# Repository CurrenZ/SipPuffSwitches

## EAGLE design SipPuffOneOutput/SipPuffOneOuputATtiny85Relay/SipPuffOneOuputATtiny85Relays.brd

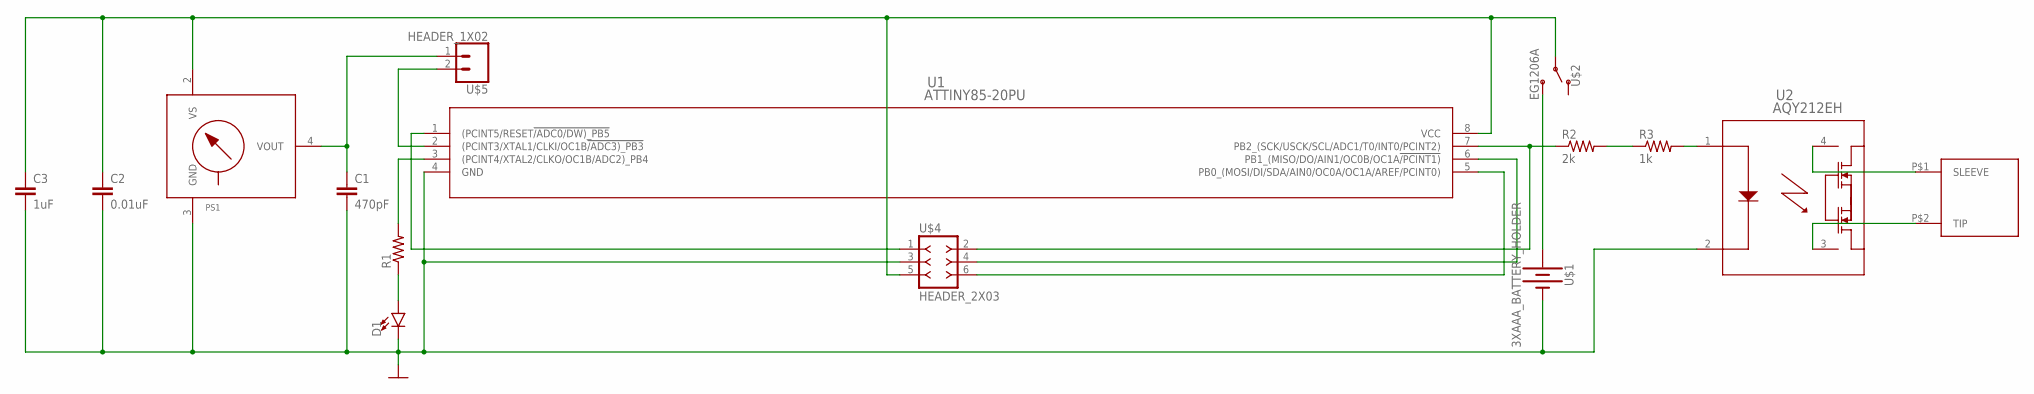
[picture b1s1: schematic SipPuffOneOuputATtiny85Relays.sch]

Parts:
C1: 470pF; CAP-PTH-SMALL-KIT
C2: 0.01uF; CAP-PTH-SMALL-KIT
C3: 1uF; CAP-PTH-SMALL-KIT
D1: LED5MM; LED_5MM
PS1: MPX-1351; 1351
R1: RESISTOR_R-US_; RESISTOR_0207/10
R2: 2k; RESISTOR_0207/10
R3: 1k; RESISTOR_0207/10
U1: ATTINY85-20PU; 8P3
U2: AQY212EH; PAN_AQY21-DIP4
U$1: 3XAAA_BATTERY_HOLDER
U$2: EG1206A
U$3: MONO_WIRE
U$4: HEADER_2X03; 2X3
U$5: HEADER_1X02; 1X02

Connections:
GND: C1.2, C2.2, C3.2, D1.K (C), PS1.3 (GND), U1.4 (GND), U2.2, U$1.P$2 (-), U$4.3
unnamed: C1.1, PS1.4 (VOUT), U$5.1
unnamed: C2.1, C3.1, PS1.2 (VS), U1.8 (VCC), U$2.2, U$4.5
unnamed: U$1.P$1 (+), U$2.3 (S)
unnamed: R1.2, U1.3 ((PCINT4/XTAL2/CLKO/OC1B/ADC2)_PB4)
unnamed: D1.A, R1.1
unnamed: R2.1, U1.7 (PB2_(SCK/USCK/SCL/ADC1/T0/INT0/PCINT2)), U$4.2
unnamed: U2.4, U$3.P$1 (SLEEVE)
unnamed: U2.3, U$3.P$2 (TIP)
unnamed: U1.1 ((PCINT5/RESET!/ADC0/DW)_PB5), U$4.1
unnamed: U1.2 ((PCINT3/XTAL1/CLKI/OC1B!/ADC3)_PB3), U$5.2
unnamed: R2.2, R3.1
unnamed: U1.6 (PB1_(MISO/DO/AIN1/OC0B/OC1A!/PCINT1)), U$4.4
unnamed: U1.5 (PB0_(MOSI/DI/SDA/AIN0/OC0A/OC1A/AREF/PC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), U$4.6
unnamed: R3.2, U2.1

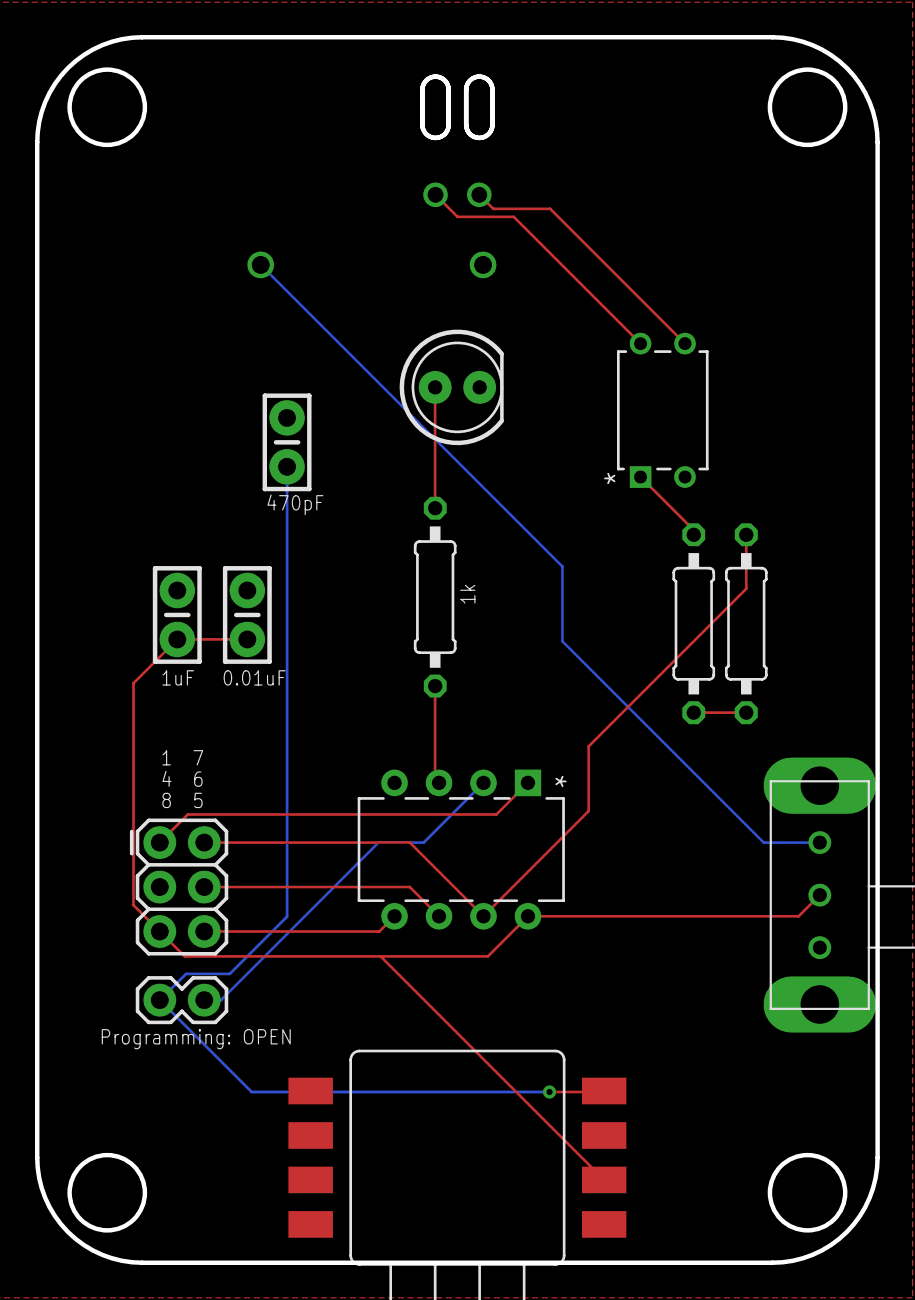
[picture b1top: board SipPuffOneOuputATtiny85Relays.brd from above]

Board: 2 copper layers, 48.0 x 70.0 mm, 15 parts (1 on the bottom side), 15 nets.

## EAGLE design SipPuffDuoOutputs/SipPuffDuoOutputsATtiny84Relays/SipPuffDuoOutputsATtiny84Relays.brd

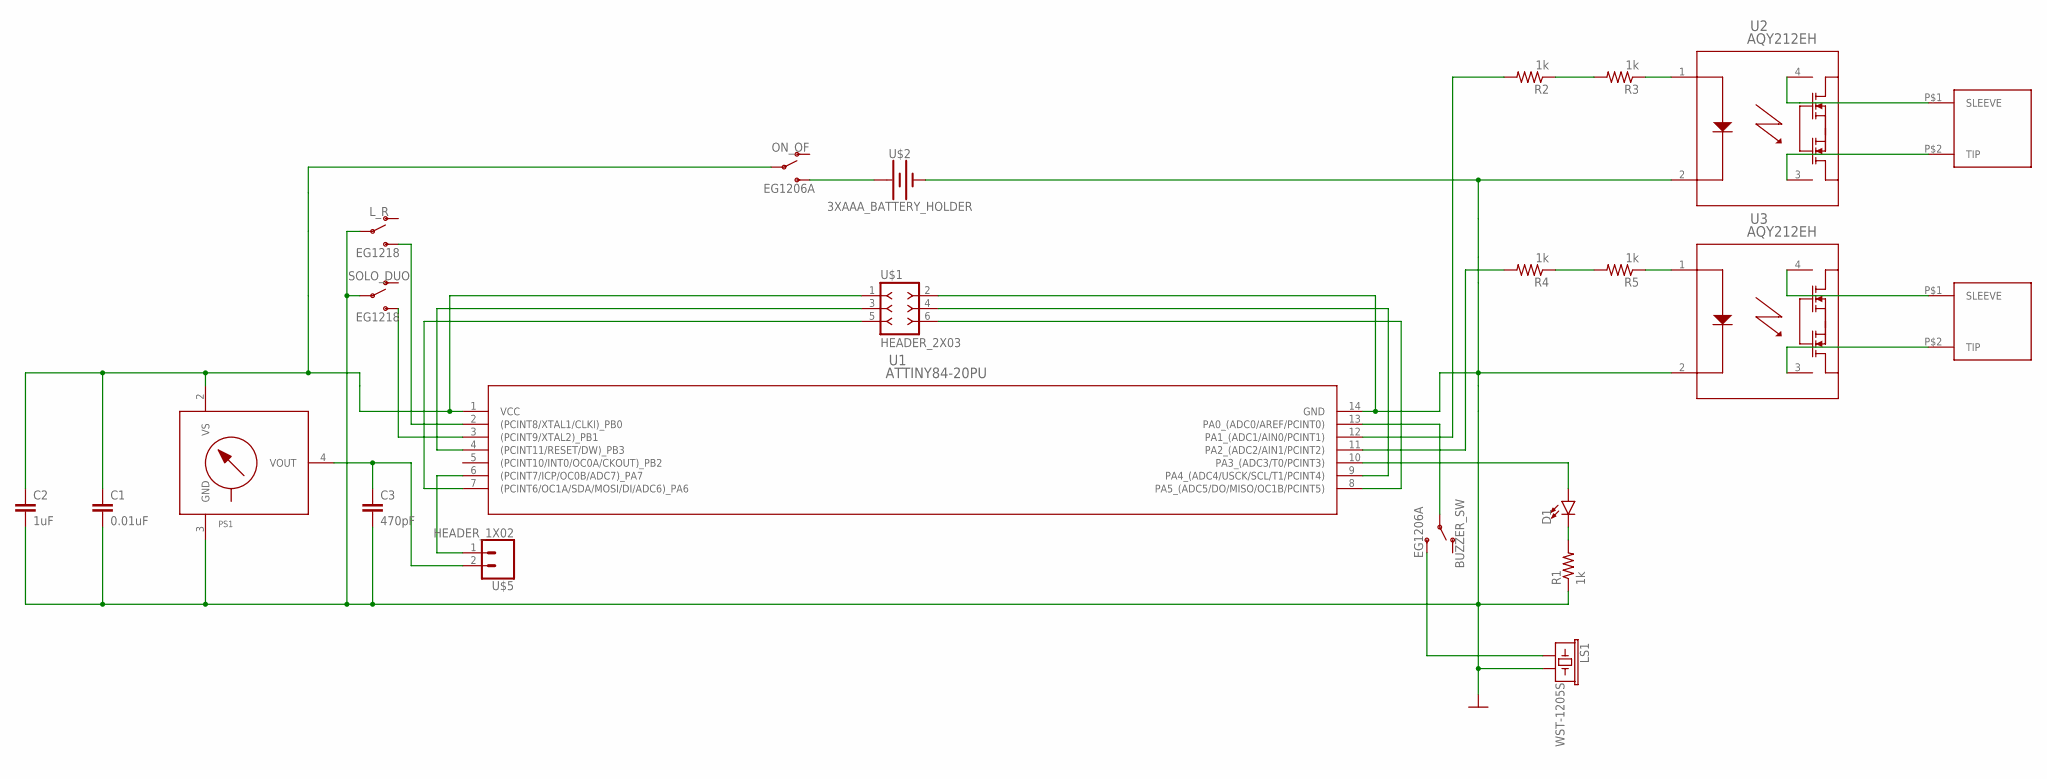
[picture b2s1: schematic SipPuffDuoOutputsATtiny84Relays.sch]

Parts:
BUZZER_SW: EG1206A
C1: 0.01uF; CAP-PTH-SMALL-KIT
C2: 1uF; CAP-PTH-SMALL-KIT
C3: 470pF; CAP-PTH-SMALL-KIT
D1: LED5MM; LED_5MM
LS1: WST-1205S; BUZZER-12MM
L_R: EG1218
ON_OF: EG1206A
PS1: MPX-1351; 1351
R1, R2, R3, R4, R5: 1k; RESISTOR_0207/10
SOLO_DUO: EG1218
U1: ATTINY84-20PU; 14P3
U2, U3: AQY212EH; PAN_AQY21-DIP4
U$1: HEADER_2X03; 2X3
U$2: 3XAAA_BATTERY_HOLDER
U$3, U$4: MONO_WIRE
U$5: HEADER_1X02; 1X02

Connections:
5V: C1.1, C2.1, ON_OF.2, PS1.2 (VS), U1.1 (VCC), U$1.1
GND: C1.2, C2.2, C3.2, LS1.- (2), L_R.2, PS1.3 (GND), R1.1, SOLO_DUO.2, U1.14 (GND), U2.2, U3.2, U$1.2, U$2.P$2 (-)
MPXVOUT: C3.1, PS1.4 (VOUT), U$5.2
unnamed: D1.A, U1.10 (PA3_(ADC3/T0/PCINT3))
unnamed: R2.2, U1.12 (PA1_(ADC1/AIN0/PCINT1))
unnamed: L_R.3 (S), U1.2 ((PCINT8/XTAL1/CLKI)_PB0)
unnamed: R4.2, U1.11 (PA2_(ADC2/AIN1/PCINT2))
unnamed: SOLO_DUO.3 (S), U1.3 ((PCINT9/XTAL2)_PB1)
unnamed: U1.8 (PA5_(ADC5/DO/MISO/OC1B/PCINT5)), U$1.6
unnamed: D1.K (C), R1.2
unnamed: U1.4 ((PCINT11/RESET/DW)_PB3), U$1.3
unnamed: U1.9 (PA4_(ADC4/USCK/SCL/T1/PCINT4)), U$1.4
unnamed: U1.7 ((PCINT6/OC1A/SDA/MOSI/DI/ADC6)_PA6), U$1.5
unnamed: ON_OF.3 (S), U$2.P$1 (+)
unnamed: BUZZER_SW.3 (S), LS1.+ (1)
unnamed: BUZZER_SW.2, U1.13 (PA0_(ADC0/AREF/PCINT0))
unnamed: U2.4, U$3.P$1 (SLEEVE)
unnamed: U2.3, U$3.P$2 (TIP)
unnamed: U3.4, U$4.P$1 (SLEEVE)
unnamed: U3.3, U$4.P$2 (TIP)
unnamed: U1.6 ((PCINT7/ICP/OC0B/ADC7)_PA7), U$5.1
unnamed: R2.1, R3.2
unnamed: R3.1, U2.1
unnamed: R4.1, R5.2
unnamed: R5.1, U3.1

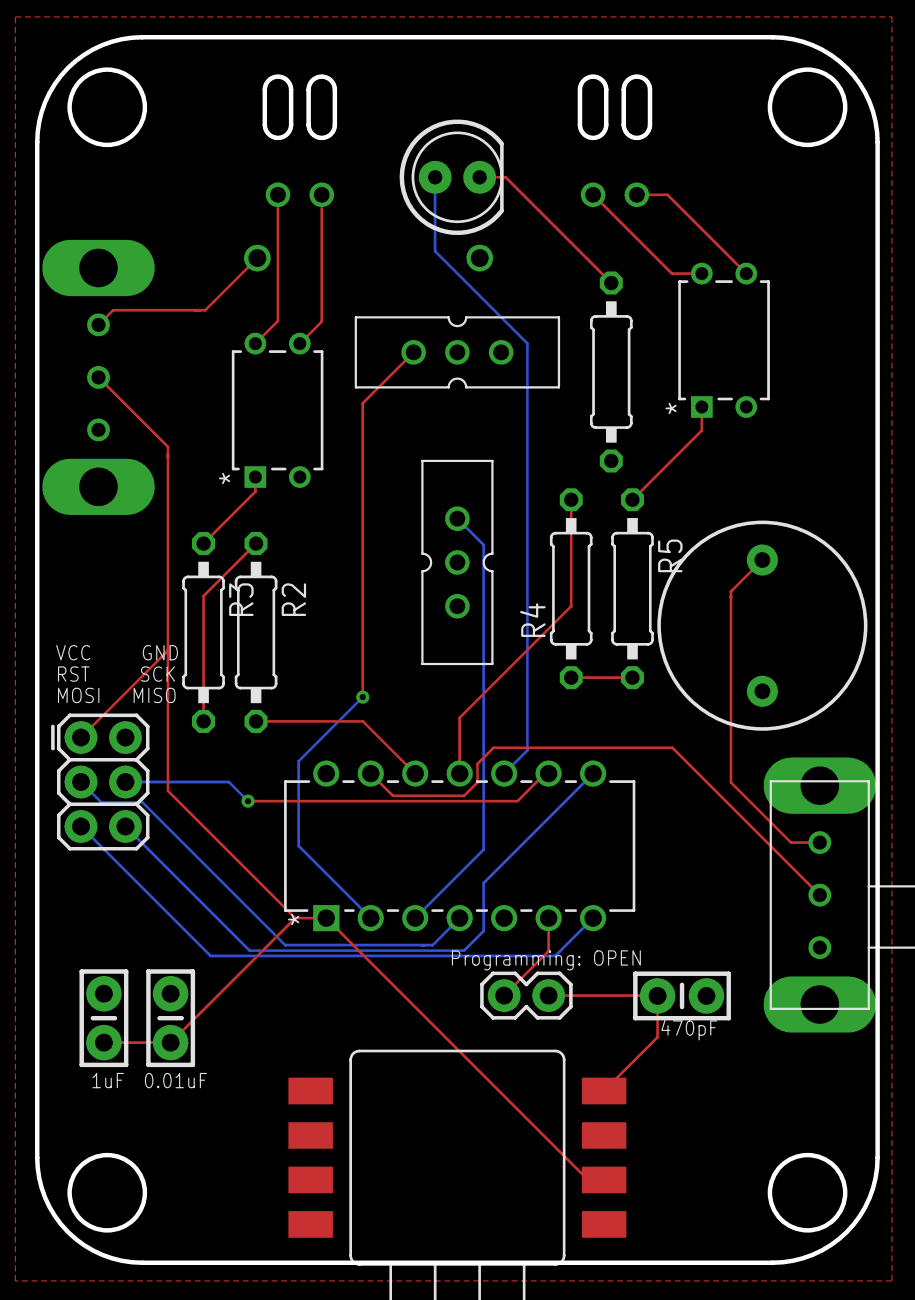
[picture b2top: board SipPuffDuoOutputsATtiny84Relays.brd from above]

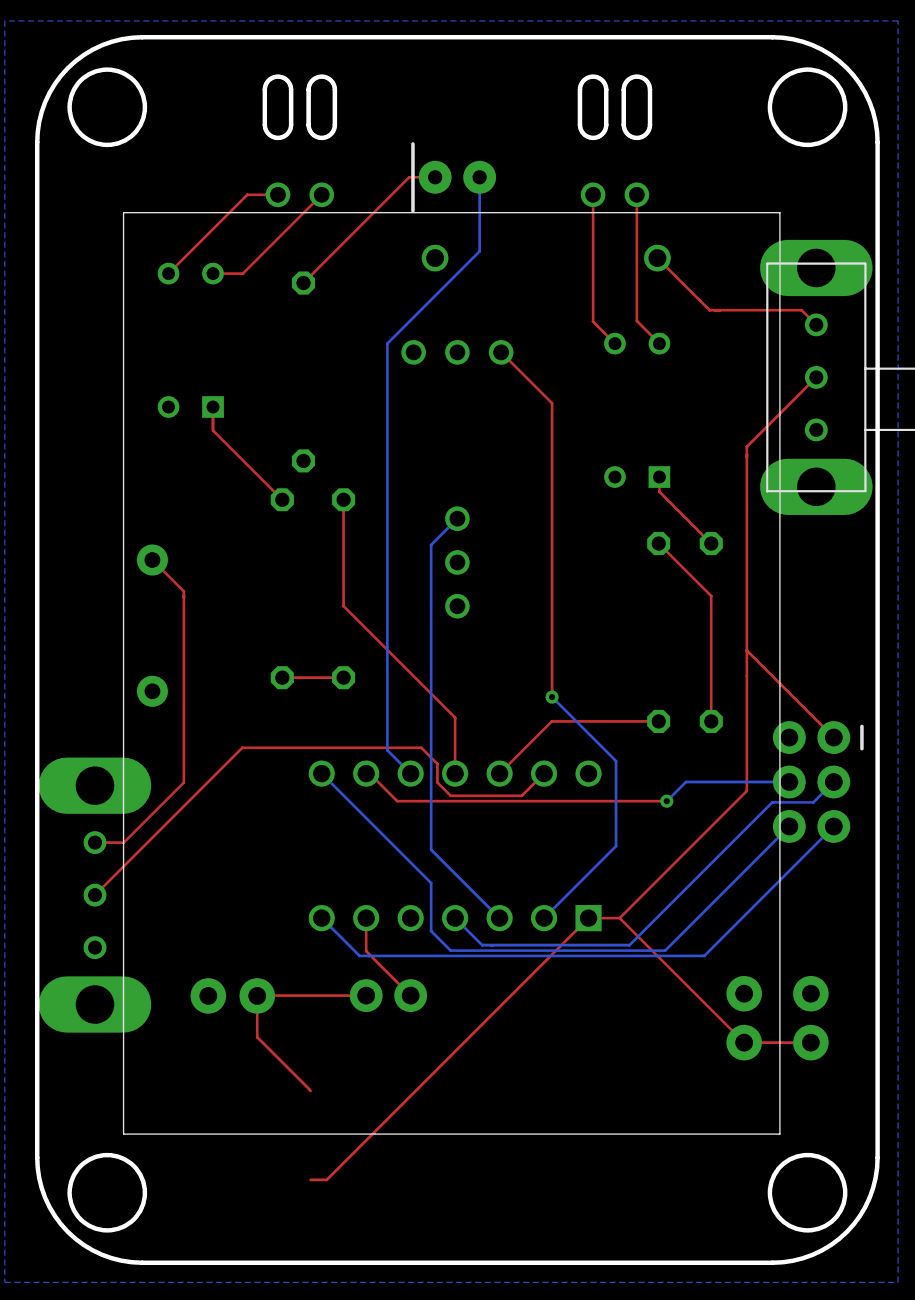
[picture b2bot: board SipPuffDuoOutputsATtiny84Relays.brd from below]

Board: 2 copper layers, 48.0 x 70.0 mm, 23 parts (2 on the bottom side), 25 nets.

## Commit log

2018-08-16 3D files added
2018-09-07 Firmwares updated
    Firmware updated, PDF schematics added
2018-09-20 Changed resistors size
